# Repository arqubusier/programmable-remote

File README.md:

# Get project

git clone  --recurse-submodules git@github.com:arqubusier/programmable-remote.git

# Build using docker

    $ cd <project-root>

Build docker image like so:

    $ docker build -t stm32-cpp-bare .

Run the container:

    $ docker run -it --name stm32-cpp-bare -p 4444:4444 -v "$(pwd)":/usr/src/app --privileged -v /dev/bus/usb:/dev/bus/usb stm32-cpp-bare /bin/bash

If you stop the container, you can start it again with:

    $ docker start -a -i stm32-cpp-bare

The project root directory on the host machine and "/usr/src/app" in the container can be used to share data.

## First-time setup

In the container run:

  root@mycontainer $ make -C libopencm3

## Build

In the container run:

  root@mycontainer $ make -C src

## Flashing

This project is currently only tested for the "bluepill" devboard.
In the container run:

  root@mycontainer $ openocd -f bluepill.cfg -c "program src/programmable-remote.elf verify reset exit"

## compile and flash using running openocd server

Start openocd server

  root@mycontainer openocd -f bluepill.cfg
  
Build and flash:

DOES NOT WORK
  root@mycontainer make -C src && echo "program src/programmable-remote.elf verify reset" | telnet localhost 4444
  
  reset halt
  stm32f1x mass_erase 0
  flash write_bank 0 src/programmable-remote.bin 0
  reset halt
  
## Write protection error

Solve using 

  reset halt; stm32f1x unlock 0

## Debug with openocd and gdb

  root@mycontainer gdb-multiarch -tui --eval-command="target remote localhost:3333" src/programmable-remote.elf

## Generate compile_commands.json

  $ make -C src clean
  $ bear make -C src

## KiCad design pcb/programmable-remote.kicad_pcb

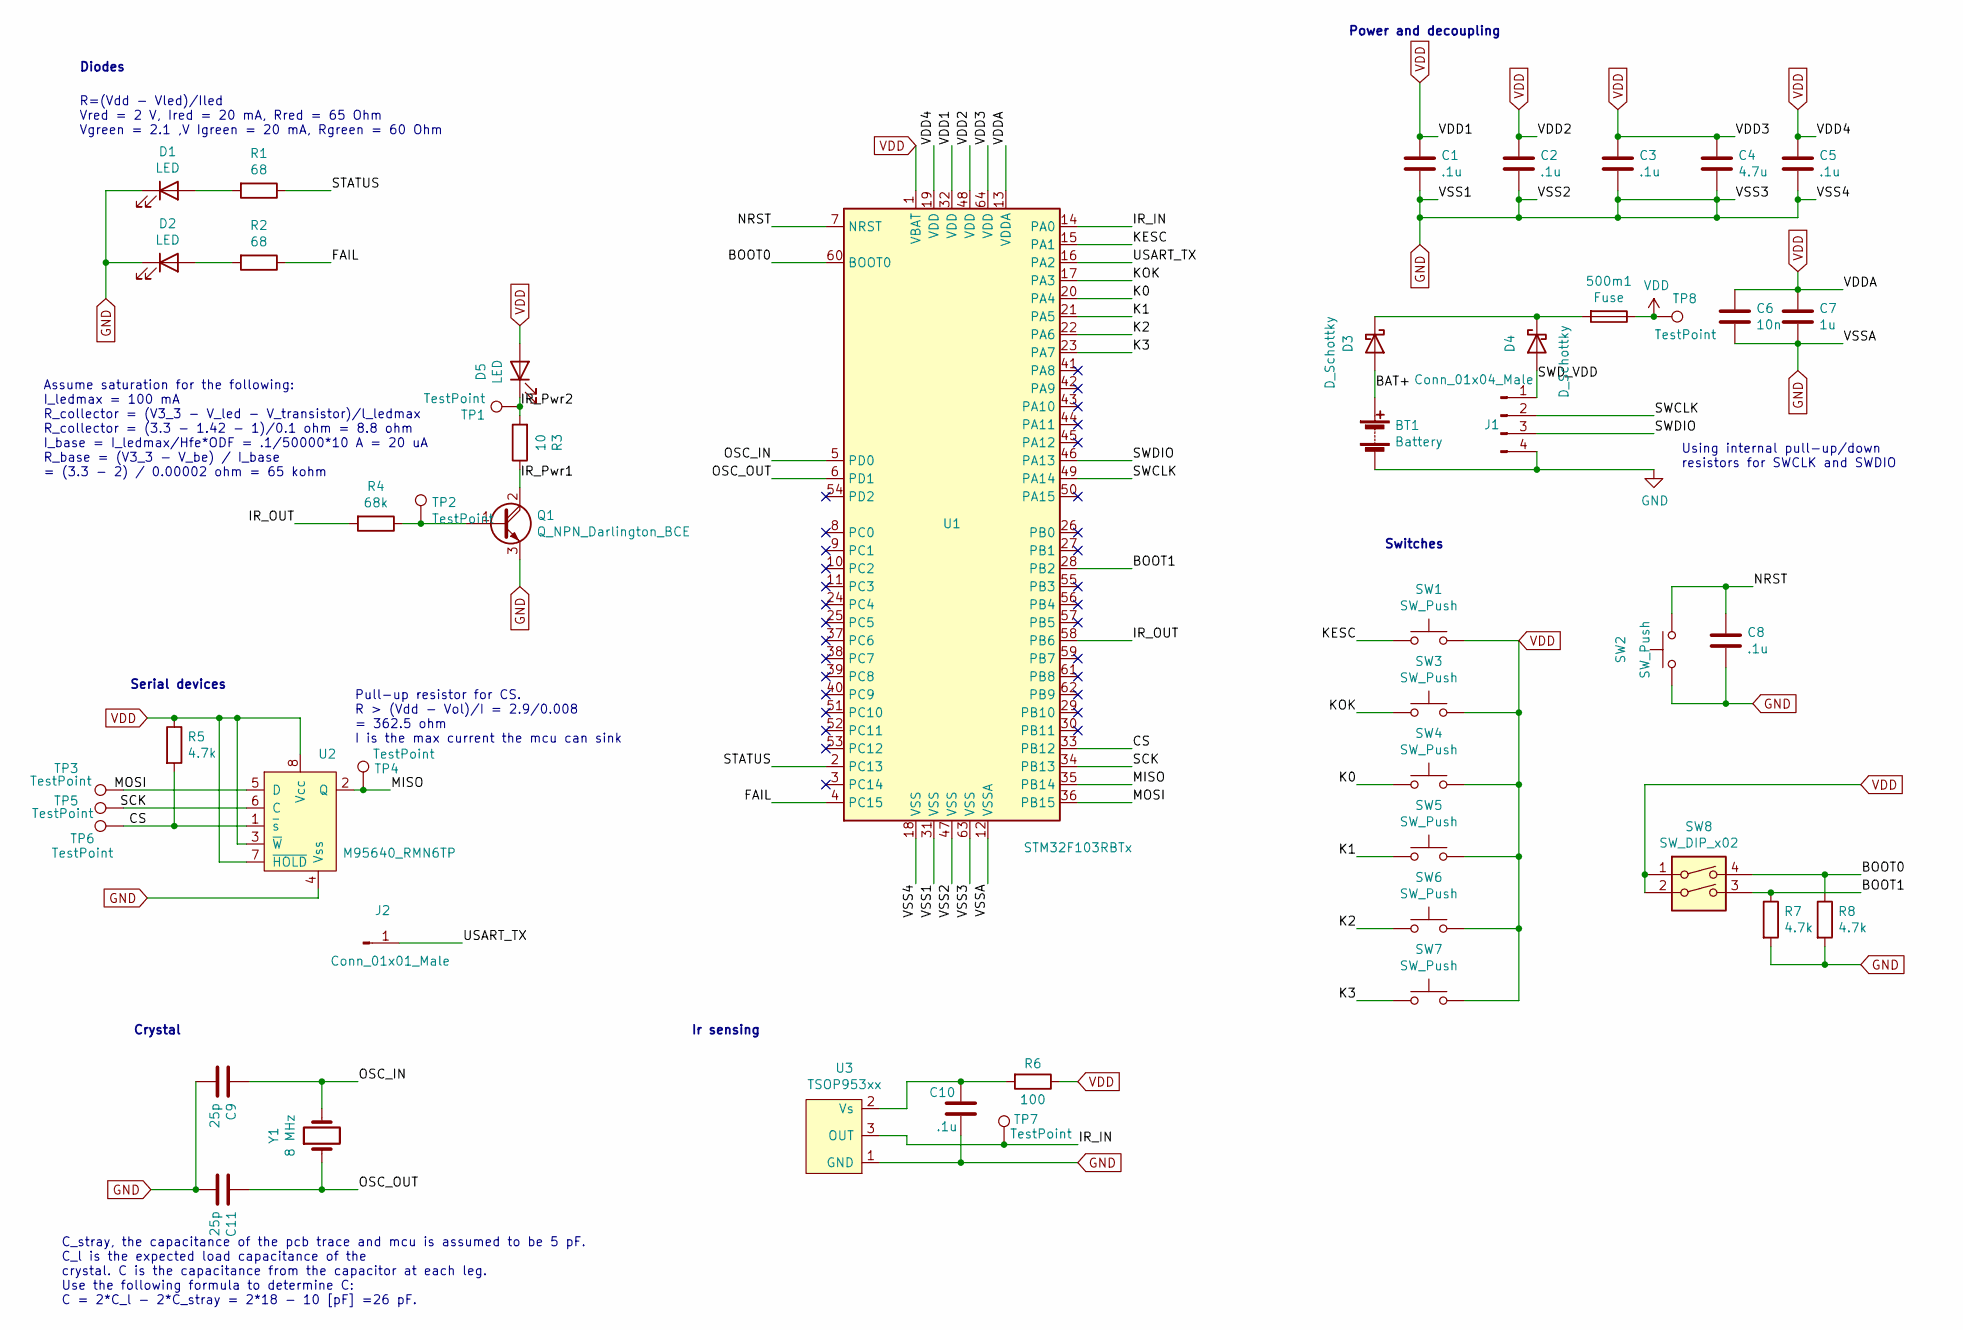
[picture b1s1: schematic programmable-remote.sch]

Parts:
500m1: Fuse; Fuse_0603_1608Metric_Pad1.05x0.95mm_HandSolder
BT1: Battery
C1, C2, C3, C5, C8, C10: .1u; C_0603_1608Metric_Pad1.08x0.95mm_HandSolder
C4: 4.7u; C_0603_1608Metric_Pad1.08x0.95mm_HandSolder
C6: 10n; C_0603_1608Metric_Pad1.08x0.95mm_HandSolder
C7: 1u; C_0603_1608Metric_Pad1.08x0.95mm_HandSolder
C9, C11: 25p; C_0603_1608Metric_Pad1.08x0.95mm_HandSolder
D1, D2: LED; C_0805_2012Metric_Pad1.18x1.45mm_HandSolder
D3, D4: D_Schottky; D_1206_3216Metric_Pad1.42x1.75mm_HandSolder
D5: LED; LED_D3.0mm_IRGrey
J1: Conn_01x04_Male; PinHeader_1x04_P2.54mm_Vertical
J2: Conn_01x01_Male; PinHeader_1x01_P2.54mm_Vertical
Q1: Q_NPN_Darlington_BCE; TSOT-23_HandSoldering
R1, R2: 68; R_0603_1608Metric_Pad0.98x0.95mm_HandSolder
R3: 10; R_0603_1608Metric_Pad0.98x0.95mm_HandSolder
R4: 68k; R_0603_1608Metric_Pad0.98x0.95mm_HandSolder
R5, R7, R8: 4.7k; R_0603_1608Metric_Pad0.98x0.95mm_HandSolder
R6: 100; R_0603_1608Metric_Pad0.98x0.95mm_HandSolder
SW1, SW3, SW4, SW5, SW6, SW7: SW_Push; SW_Cherry_MX_1.00u_PCB
SW2: SW_Push; SW_PTS526
SW8: SW_DIP_x02; SW_2LP
TP1, TP2, TP3, TP4, TP5, TP6, TP7, TP8: TestPoint; TestPoint_harwin_S2761-46R
U1: STM32F103RBTx; LQFP-64_10x10mm_P0.5mm
U2: M95640_RMN6TP; SOIC-8_3.9x4.9mm_P1.27mm
U3: TSOP953xx
Y1: 8 MHz; Crystal_ABLS-8.000MHZ-B4-T

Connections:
/BAT+: BT1.1 (+), D3.2 (A)
/BOOT0: R8.1, SW8.4, U1.60 (BOOT0)
/BOOT1: R7.1, SW8.3, U1.28 (PB2)
/CS: R5.2, TP6.1, U1.33 (PB12), U2.1 (~s)
/FAIL: R2.1, U1.4 (PC15)
/IR_IN: TP7.1, U1.14 (PA0), U3.3 (OUT)
/IR_OUT: R4.2, U1.58 (PB6)
/IR_Pwr1: Q1.2 (C), R3.1
/IR_Pwr2: D5.1 (K), R3.2, TP1.1
/K0: SW4.1, U1.20 (PA4)
/K1: SW5.1, U1.21 (PA5)
/K2: SW6.1, U1.22 (PA6)
/K3: SW7.1, U1.23 (PA7)
/KESC: SW1.1, U1.15 (PA1)
/KOK: SW3.1, U1.17 (PA3)
/MISO: TP4.1, U1.35 (PB14), U2.2 (Q)
/MOSI: TP3.1, U1.36 (PB15), U2.5 (D)
/NRST: C8.1, SW2.2, U1.7 (NRST)
/OSC_IN: C9.1, U1.5 (PD0), Y1.2
/OSC_OUT: C11.1, U1.6 (PD1), Y1.1
/SCK: TP5.1, U1.34 (PB13), U2.6 (C)
/STATUS: R1.1, U1.2 (PC13)
/SWCLK: J1.2, U1.49 (PA14)
/SWDIO: J1.3, U1.46 (PA13)
/SWD_VDD: D4.2 (A), J1.1
/USART_TX: J2.1, U1.16 (PA2)
GND: BT1.2 (-), C1.2, C2.2, C3.2, C4.2, C5.2, C6.2, C7.2, C8.2, C9.2, C10.2, C11.2, D1.1 (K), D2.1 (K), J1.4, Q1.3 (E), R7.2, R8.2, SW2.1, U1.12 (VSSA), U1.18 (VSS), U1.31 (VSS), U1.47 (VSS), U1.63 (VSS), U2.4 (Vss), U3.1 (GND)
unnamed: 500m1.2, D3.1 (K), D4.1 (K)
unnamed: C10.1, R6.2, U3.2 (Vs)
unnamed: D1.2 (A), R1.2
unnamed: D2.2 (A), R2.2
unnamed: Q1.1 (B), R4.1, TP2.1
VDD: 500m1.1, C1.1, C2.1, C3.1, C4.1, C5.1, C6.1, C7.1, D5.2 (A), R5.1, R6.1, SW1.2, SW3.2, SW4.2, SW5.2, SW6.2, SW7.2, SW8.1, SW8.2, TP8.1, U1.1 (VBAT), U1.13 (VDDA), U1.19 (VDD), U1.32 (VDD), U1.48 (VDD), U1.64 (VDD), U2.3 (~W), U2.7 (~HOLD), U2.8 (Vcc)

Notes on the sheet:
R=(Vdd - Vled)/Iled Vred = 2 V, Ired = 20 mA, Rred = 65 Ohm Vgreen = 2.1 ,V Igreen = 20 mA, Rgreen = 60 Ohm
Power and decoupling
Diodes
Switches
Crystal
Ir sensing
C_stray, the capacitance of the pcb trace and mcu is assumed to be 5 pF. C_l is the expected load capacitance of the crystal. C is the capacitance from the capacitor at each leg. Use the following formula to determine C: C = 2*C_l - 2*C_stray = 2*18 - 10 [pF] =26 pF.
Serial devices
Assume saturation for the following: I_ledmax = 100 mA R_collector = (V3_3 - V_led - V_transistor)/l_ledmax R_collector = (3.3 - 1.42 - 1)/0.1 ohm = 8.8 ohm I_base = I_ledmax/Hfe*ODF = .1/50000*10 A = 20 uA R_base = (V3_3 - V_be) / I_base = (3.3 - 2) / 0.00002 ohm = 65 kohm
Pull-up resistor for CS. R > (Vdd - Vol)/I = 2.9/0.008 = 362.5 ohm I is the max current the mcu can sink
Using internal pull-up/down resistors for SWCLK and SWDIO

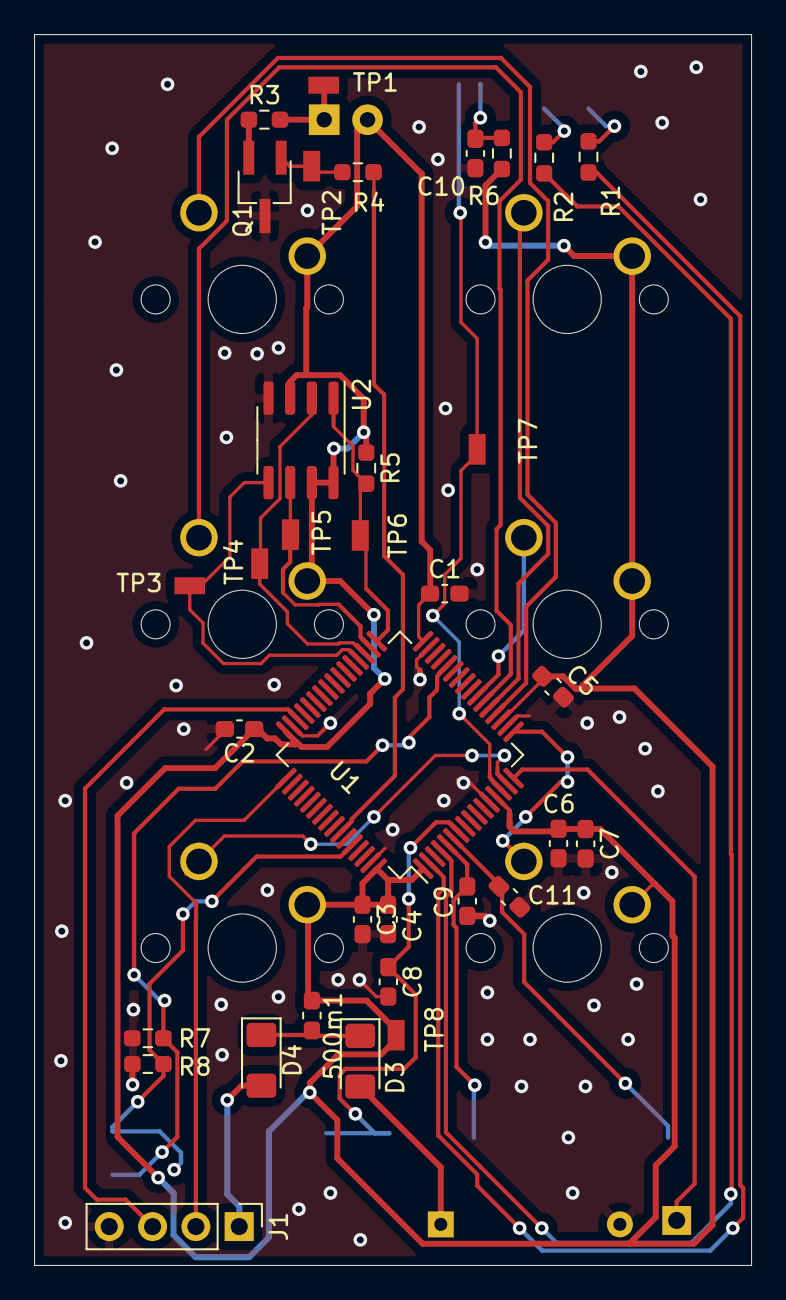
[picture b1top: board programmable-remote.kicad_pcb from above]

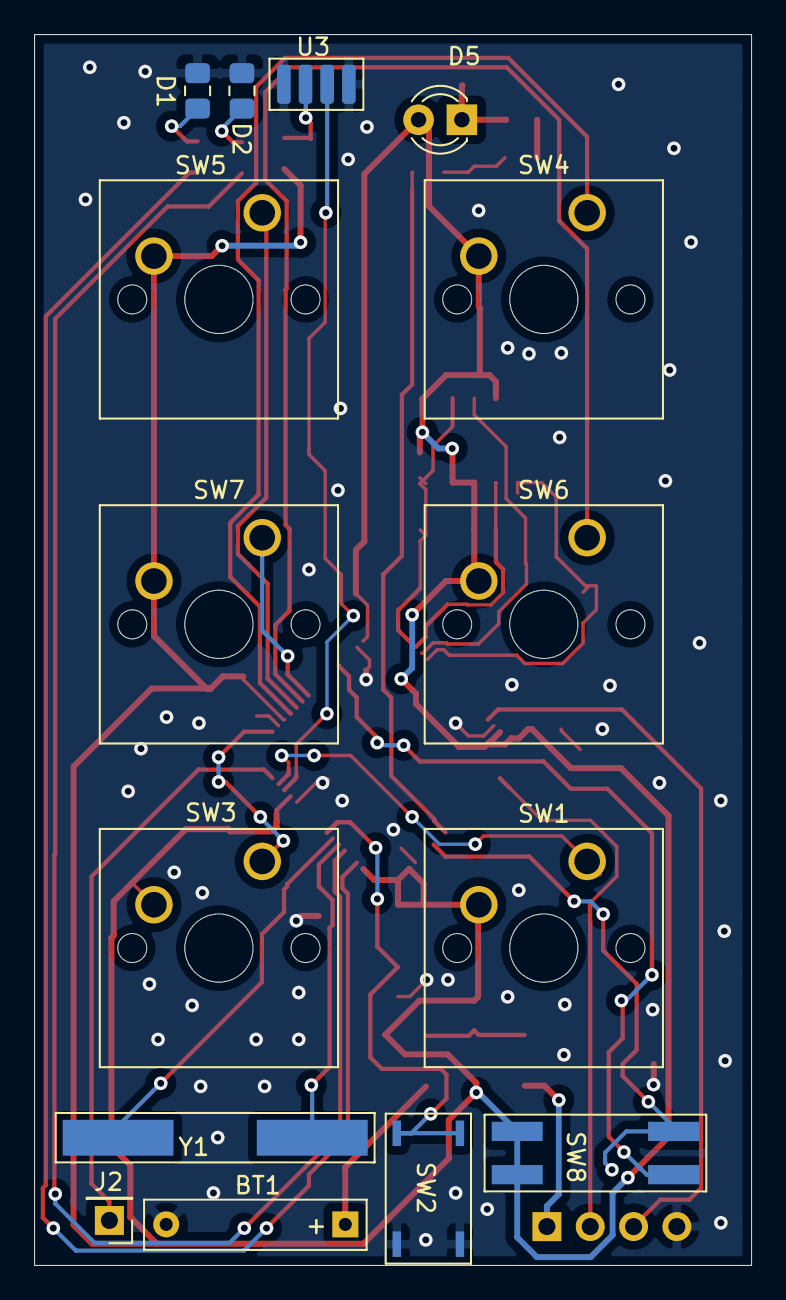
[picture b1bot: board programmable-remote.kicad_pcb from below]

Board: 2 copper layers, 42.0 x 72.2 mm, 49 parts (15 on the bottom side), 33 nets.

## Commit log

2020-04-19 Adapted libopencm3 template
2020-04-19 Added interrupt, problems triggering consitently.
2020-04-26 Added working timer example and fixed interrupt issue.
2020-04-27 Trying to output timer WIP.
2020-04-27 Output from timer on pin :)
2020-05-01 approximate 38kHz pulse with TIM2.
2020-05-01 Cleanup, Output on TIM2 and TIM3 working.
2020-05-01 Minor correction
2020-05-02 Input interrupt.
2020-05-02 Ir handling skeleton.
2020-05-03 Command timer timing correct.
2020-05-03 Changing ir handling WIP.
2020-05-04 fixed compilation errors.
2020-05-09 Added catch2.
2020-05-09 ns2count passing.
2020-05-09 State machine for InputHandler works.
2020-05-10 InputHandler parsing working.
2020-05-10 Refactoring. Problem with EXTI interrupt not triggering a second time.
2020-05-11 restarting from timer example.
2020-05-12 wip2
2020-05-12 tim3 working.
2020-05-12 tim3 still works.
2020-05-12 cleanup. tim3 works.
2020-05-12 more cleanup, prescaler calculation has to be done manually.
2020-05-13 Timer interrupt too soon.
2020-05-14 Workaround works except for first delta which is about half the expected.
2020-05-15 Fixed issue with wrongly configured period.
2020-05-16 Started with outputhandler.
2020-05-16 OutputHandler interrupt triggers.
2020-05-17 Added missing reset for outputhandler.
2020-05-17 Output handler working as expected for small example.
2020-05-21 Wrote simple try_lock.
2020-05-23 Projector menu command tested and working.
2020-05-24 Started with main statecmachine logic.
2020-05-28 Restarted with statemachine.
2020-05-30 More work on statemachine.
2020-05-30 Statemachine prototype.
2020-05-30 File restructuring
2020-05-31 Added googletest.
2020-05-31 Moved tests from catch to googletest.
2020-06-01 Added gmock.
2020-06-02 Fixed template substitution error.
2020-06-02 Fixed link errors.
2020-06-06 Sending move operations, and Statemachine tests.
2020-06-07 Altered statemachine.
2020-06-13 Mocking functions used by input handler.
2020-06-14 Compliation errors.
2020-06-20 Fixed issues in test.
2020-06-21 Sending tests passes.
2020-06-23 Wrote tests for 'SelectingProgram' and 'Receiving'.
2020-06-28 SelectingProgram tests passes.
2020-06-28 Receiving tests passing.
2020-07-21 Fixed compliation issues for device, issue with ram size.
2020-07-22 Fixed the ram size issue.
2020-08-09 Added hard_fault handler, problem with hardfault.
2021-05-02 Added state diagram.
2021-05-09 Added docker and sml.
2021-05-09 Updated license.
2021-05-09 Began redesign.
2021-05-09 sml proof of concept.
2021-05-09 Removed etl.
2021-05-19 Problem with flashing a2.
2021-05-19 Debounce timer works for tim3 but not tim5.
2021-05-20 Documentation update
2021-05-20 clang-format
2021-05-20 debounce timer correct behaivour.
2021-05-22 Added debounce diagram.
2021-05-23 Prototype debouncing, not tested.
2021-05-26 Consume button bounce interrutps. Problem with consecutive presses.
2021-05-30 Usart2 working
2021-05-30 Debounce working.
2021-05-31 Cleanup
2021-06-01 six buttons.
2021-06-01 Template buttons.
2021-06-06 move led pin.
2021-06-07 Started on rx sm.
2021-06-12 Rx state machine.
2021-06-12 Type rename.
2021-06-13 Fixed bug in button_setup and delay
2021-06-13 All buttons working :)
2021-06-13 missing interrupt flag clearing.
2021-06-14 Clean design doc.
2021-06-20 Prototype rx
2021-06-20 Rx working.
2021-08-02 Update state machine documentation.
2021-08-02 Skeleton for tx states.
2021-08-03 Tx statemachine prototype.
2021-08-03 Cannot get interrupt from tim2.
2021-08-04 Tim2 interrupting.
2021-08-04 Timing for multiple commands working, except for 2 initial segments.
    For some reason there the first segment is always at least 5ms
    regardless of program.
2021-08-04 Tx looks good on scope.
2021-08-05 Remote working with projector and av, but not stereo.
2021-08-07 Added schematic.
2021-08-08 Initial schematic done.
2021-08-08 Fix drc errors.
2021-08-08 Started layout.
2021-08-11 signals routed
2021-08-11 ground pour added
2021-08-13 Pcb 1.0
2021-08-21 Started with case.
2021-08-22 minor change
2021-08-22 Restarted case with OpenScad.
2021-08-22 More work on case.
2021-08-23 Adjusted case according to pcb.
2021-08-24 Case fixes.
2021-08-31 Various changes.
